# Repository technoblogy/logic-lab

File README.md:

# Logic Lab
A board that provides 12 logic gates that you can interconnect with patch cables to make a variety of different logic circuits. This version is implemented using an AVR microcontroller:

For more information see <http://www.technoblogy.com/show?4FFY>.

Alternatively see [Logic Lab 1G](https://github.com/technoblogy/logic-lab-1g) which is functionally identical, but implemented using 12 individual logic gates.

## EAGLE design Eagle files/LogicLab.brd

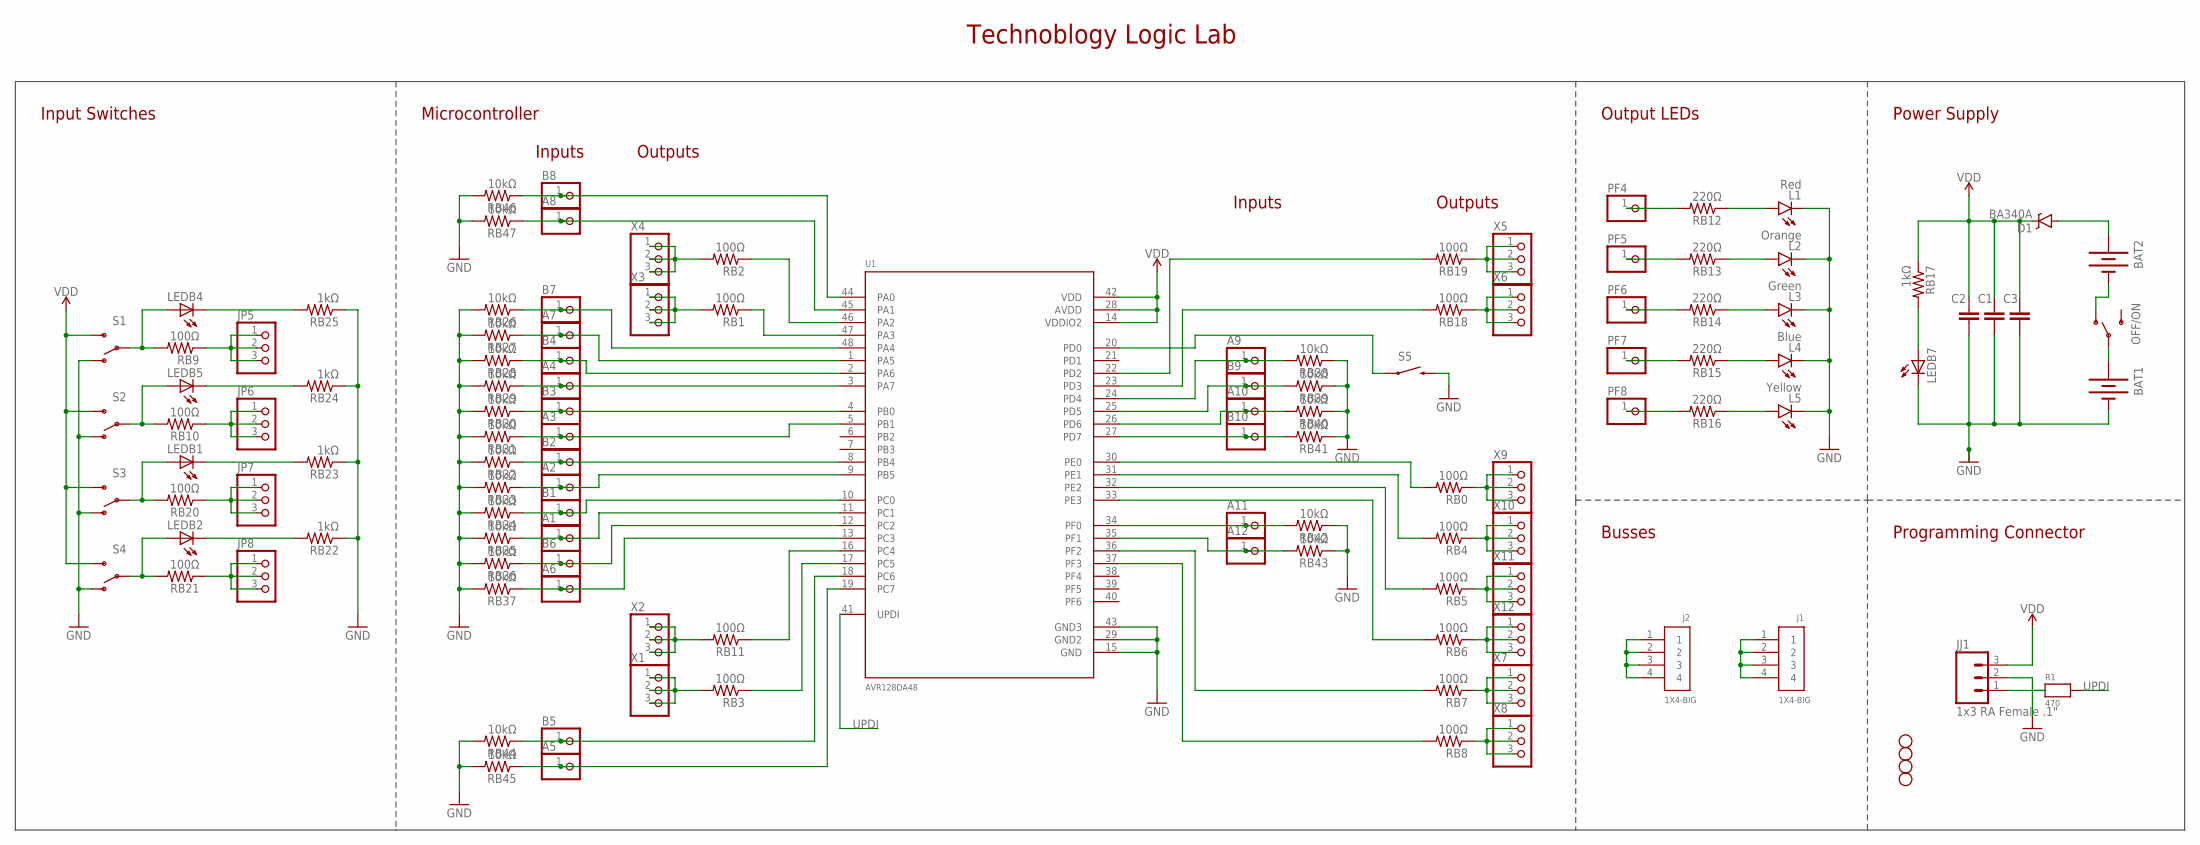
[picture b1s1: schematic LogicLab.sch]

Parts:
A1, A2, A3, A4, A5, A6, A7, A8, A9, A10, A11, A12: PINHD-1X1; 1X01
B1, B2, B3, B4, B5, B6, B7, B8, B9, B10: PINHD-1X1; 1X01
BAT1, BAT2: BATTERYAAA-KIT; BATTERY-AAA-KIT
C1, C2: 100n; 0805
C3: 10uF; 0805
D1: BA340A; SMA-DIODE
J1, J2: 1X4-BIG; 1X04-BIG
JJ1: 1x3 RA Female .1"; 1X03_SMD_RA_FEMALE
JP1, JP2, JP3, JP4: STAND-OFF
JP5, JP6, JP7, JP8: PINHD-1X3; 1X03
L1: Red; LED5MM
L2: Orange; LED5MM
L3: Green; LED5MM
L4: Blue; LED5MM
L5: Yellow; LED5MM
LEDB1, LEDB2, LEDB4, LEDB5, LEDB7: LEDCHIPLED_0805; CHIPLED_0805
OFF/ON: SWITCH-SPDTKIT; SWITCH-SPDT_KIT
PF4, PF5, PF6, PF7, PF8: PINHD-1X1; 1X01
R1: 470; _0805MP
RB0, RB1, RB2, RB3, RB4, RB5, RB6, RB7, RB8, RB9, RB10, RB11, RB18, RB19, RB20, RB21: 100Ω; 0805
RB12, RB13, RB14, RB15, RB16: 220Ω; 0805
RB17, RB22, RB23, RB24, RB25: 1kΩ; 0805
RB26, RB27, RB28, RB29, RB30, RB31, RB32, RB33, RB34, RB35, RB36, RB37, RB38, RB39, RB40, RB41, RB42, RB43, RB44, RB45, RB46, RB47: 10kΩ; 0805
S1, S2, S3, S4: SWITCH-SPDTKIT; SWITCH-SPDT_KIT
S5: SWITCH-MOMENTARY-2SMD-4.6X2.8MM; TACTILE_SWITCH_SMD_4.6X2.8MM
U1: AVR128DA48; LQFP48
X1, X2, X3, X4, X5, X6, X7, X8, X9, X10, X11, X12: PINHD-1X3; 1X03

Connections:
COM: BAT1.PWR@1 (+), OFF/ON.2
GND: BAT1.GND@1 (-), C1.2, C2.2, C3.2, JJ1.2, L1.K (C), L2.K (C), L3.K (C), L4.K (C), L5.K (C), LEDB7.C, RB22.1, RB23.1, RB24.1, RB25.1, RB26.2, RB27.2, RB28.2, RB29.2, RB30.2, RB31.2, RB32.2, RB33.2, RB34.2, RB35.2, RB36.2, RB37.2, RB38.1, RB39.1, RB40.1, RB41.1, RB42.1, RB43.1, RB44.2, RB45.2, RB46.2, RB47.2, S1.1 (O), S2.1 (O), S3.1 (O), S4.1 (O), S5.3 (2), S5.4 (2), U1.15 (GND), U1.29 (GND2), U1.43 (GND3)
unnamed: A7.1, RB27.1, U1.1 (PA5)
unnamed: RB18.1, X6.1, X6.2, X6.3
unnamed: RB19.1, X5.1, X5.2, X5.3
unnamed: B4.1, RB28.1, U1.2 (PA6)
unnamed: PF4.1, RB12.2
unnamed: PF5.1, RB13.2
unnamed: PF6.1, RB14.2
unnamed: B10.1, RB41.2, U1.27 (PD7)
unnamed: A10.1, RB40.2, U1.26 (PD6)
unnamed: RB18.2, U1.23 (PD3)
unnamed: A4.1, RB29.1, U1.3 (PA7)
unnamed: PF7.1, RB15.2
unnamed: BAT2.PWR@1 (+), D1.A
unnamed: RB0.1, X9.1, X9.2, X9.3
unnamed: A1.1, RB35.1, U1.11 (PC1)
unnamed: S5.1, S5.2 (1), U1.20 (PD0)
unnamed: RB4.1, X10.1, X10.2, X10.3
unnamed: B6.1, RB36.1, U1.12 (PC2)
unnamed: RB19.2, U1.22 (PD2)
unnamed: A9.1, RB38.2, U1.24 (PD4)
unnamed: B9.1, RB39.2, U1.25 (PD5)
unnamed: B3.1, RB30.1, U1.4 (PB0)
unnamed: A3.1, RB31.1, U1.5 (PB1)
unnamed: B8.1, RB46.1, U1.44 (PA0)
unnamed: A6.1, RB37.1, U1.13 (PC3)
unnamed: B1.1, RB34.1, U1.10 (PC0)
unnamed: RB5.1, X11.1, X11.2, X11.3
unnamed: RB11.1, U1.16 (PC4)
unnamed: A2.1, RB33.1, U1.9 (PB5)
unnamed: B2.1, RB32.1, U1.8 (PB4)
unnamed: B5.1, RB44.1, U1.18 (PC6)
unnamed: RB6.1, X12.1, X12.2, X12.3
unnamed: A5.1, RB45.1, U1.19 (PC7)
unnamed: LEDB4.A, RB9.2, S1.2
unnamed: B7.1, RB26.1, U1.48 (PA4)
unnamed: A8.1, RB47.1, U1.45 (PA1)
unnamed: RB7.1, X7.1, X7.2, X7.3
unnamed: RB1.1, U1.47 (PA3)
unnamed: LEDB5.A, RB10.2, S2.2
unnamed: RB2.1, U1.46 (PA2)
unnamed: RB3.1, U1.17 (PC5)
unnamed: RB0.2, U1.30 (PE0)
unnamed: RB4.2, U1.31 (PE1)
unnamed: RB5.2, U1.32 (PE2)
unnamed: RB6.2, U1.33 (PE3)
unnamed: RB8.1, X8.1, X8.2, X8.3
unnamed: A11.1, RB42.2, U1.34 (PF0)
unnamed: A12.1, RB43.2, U1.35 (PF1)
unnamed: PF8.1, RB16.2
unnamed: RB7.2, U1.36 (PF2)
unnamed: RB8.2, U1.37 (PF3)
unnamed: LEDB1.A, RB20.2, S3.2
unnamed: LEDB2.A, RB21.2, S4.2
unnamed: RB11.2, X2.1, X2.2, X2.3
unnamed: RB3.2, X1.1, X1.2, X1.3
unnamed: RB2.2, X4.1, X4.2, X4.3
unnamed: RB1.2, X3.1, X3.2, X3.3
unnamed: L1.A, RB12.1
unnamed: L2.A, RB13.1
unnamed: L3.A, RB14.1
unnamed: L4.A, RB15.1
unnamed: L5.A, RB16.1
unnamed: JP8.1, JP8.2, JP8.3, RB21.1
unnamed: JP7.1, JP7.2, JP7.3, RB20.1
unnamed: LEDB7.A, RB17.2
unnamed: J2.1, J2.2, J2.3, J2.4
unnamed: JP6.1, JP6.2, JP6.3, RB10.1
unnamed: LEDB2.C, RB22.2
unnamed: LEDB1.C, RB23.2
unnamed: JP5.1, JP5.2, JP5.3, RB9.1
unnamed: LEDB4.C, RB25.2
unnamed: LEDB5.C, RB24.2
unnamed: JJ1.1, R1.1
unnamed: J1.1, J1.2, J1.3, J1.4
ON: BAT2.GND@1 (-), OFF/ON.1 (O)
UPDI: R1.2, U1.41 (UPDI)
VDD: C1.1, C2.1, C3.1, D1.C, JJ1.3, RB17.1, S1.3 (S), S2.3 (S), S3.3 (S), S4.3 (S), U1.14 (VDDIO2), U1.28 (AVDD), U1.42 (VDD)

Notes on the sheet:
Technoblogy Logic Lab
Input Switches
Microcontroller
Output LEDs
Power Supply
Inputs
Outputs
Programming Connector
Busses

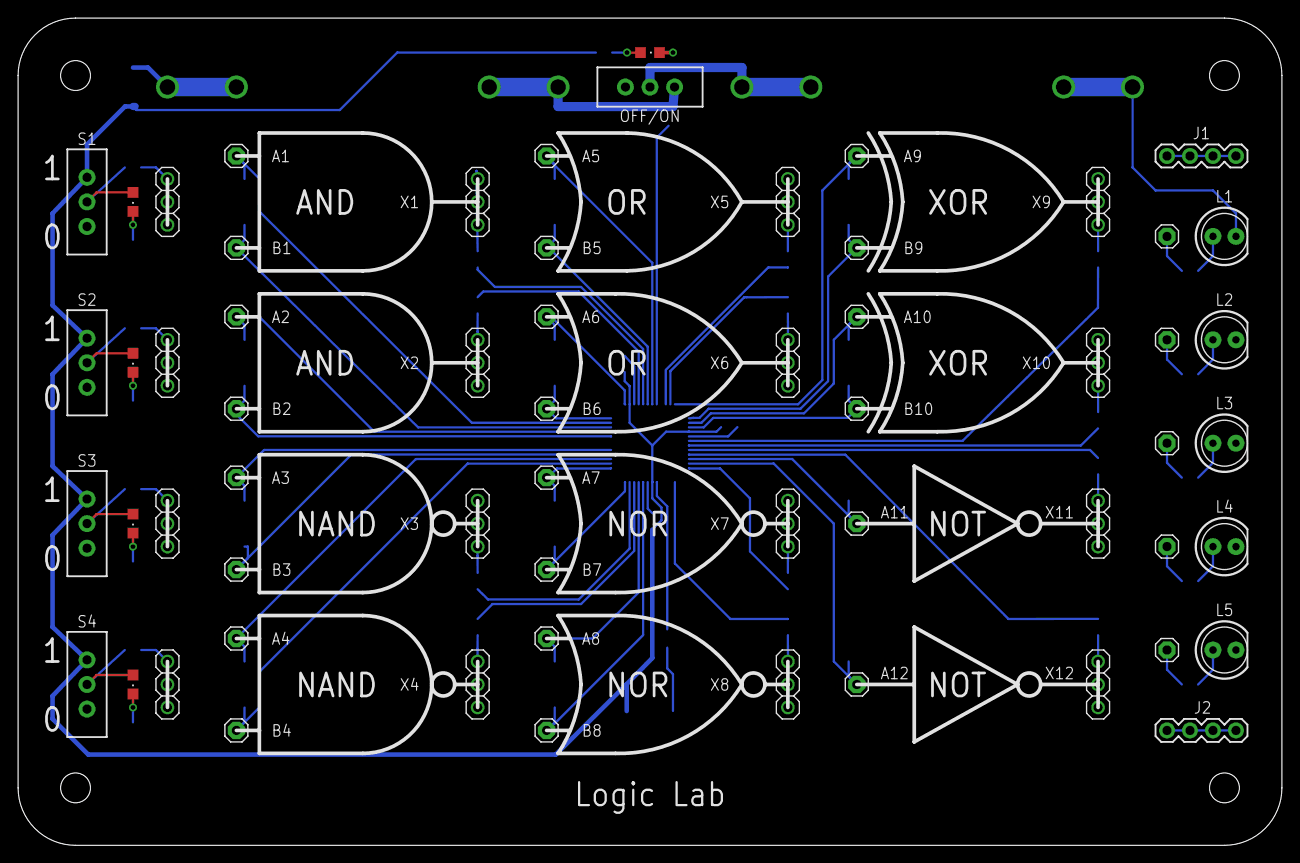
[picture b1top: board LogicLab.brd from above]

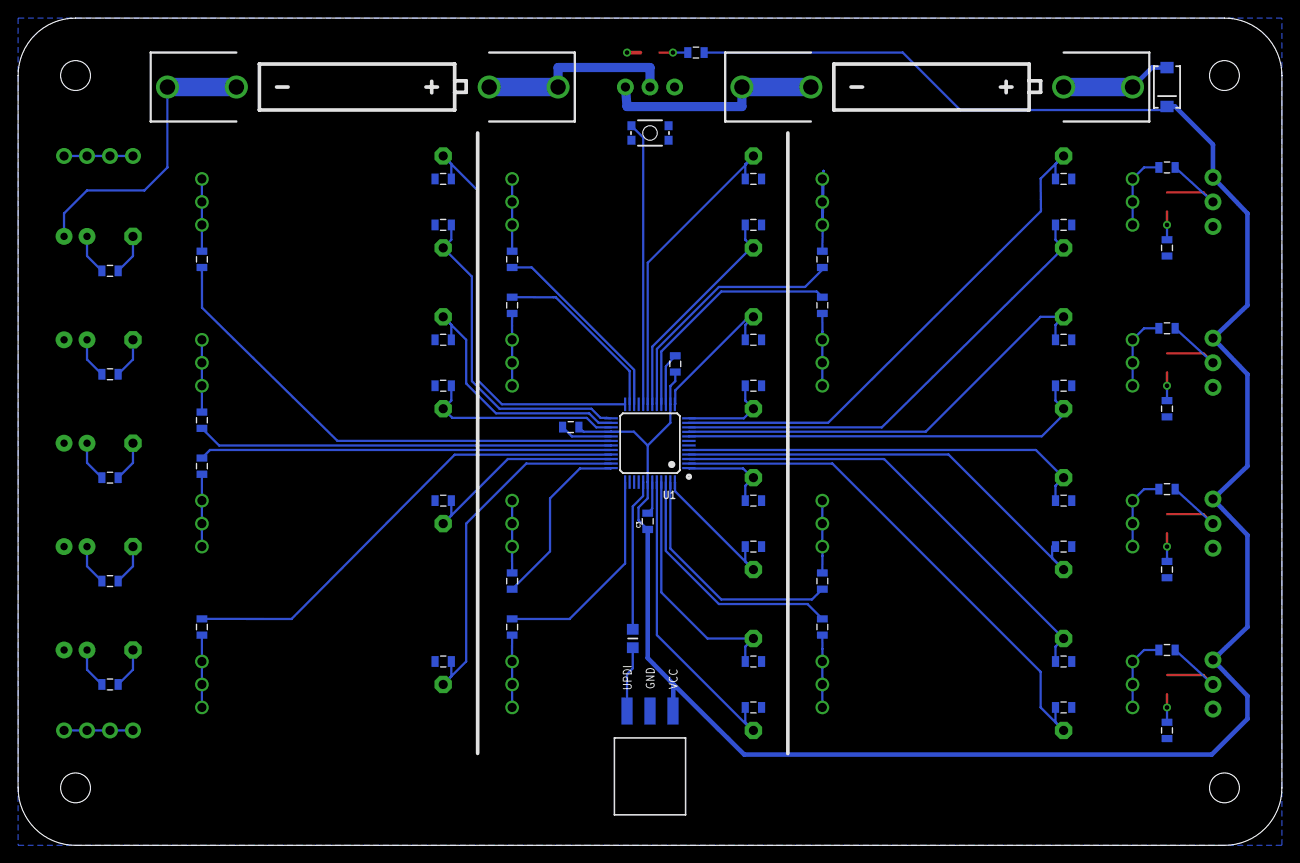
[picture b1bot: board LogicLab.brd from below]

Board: 2 copper layers, 139.7 x 91.4 mm, 122 parts (58 on the bottom side), 79 nets.

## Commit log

2023-05-18 Version 1 - 18th May 2023
2023-05-24 Version 1 - 18th May 2023
    Added Gerber files
2026-02-28 CC BY-SA 4.0

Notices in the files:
parts and their libraries:
SparkFun-Electromechanical: Licensing: Creative Commons ShareAlike 4.0 International - https://creativecommons.org/licenses/by-sa/4.0
microbuilder: This work is placed in the public domain, and may be freely used for commercial and non-commercial work with the following conditions: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
